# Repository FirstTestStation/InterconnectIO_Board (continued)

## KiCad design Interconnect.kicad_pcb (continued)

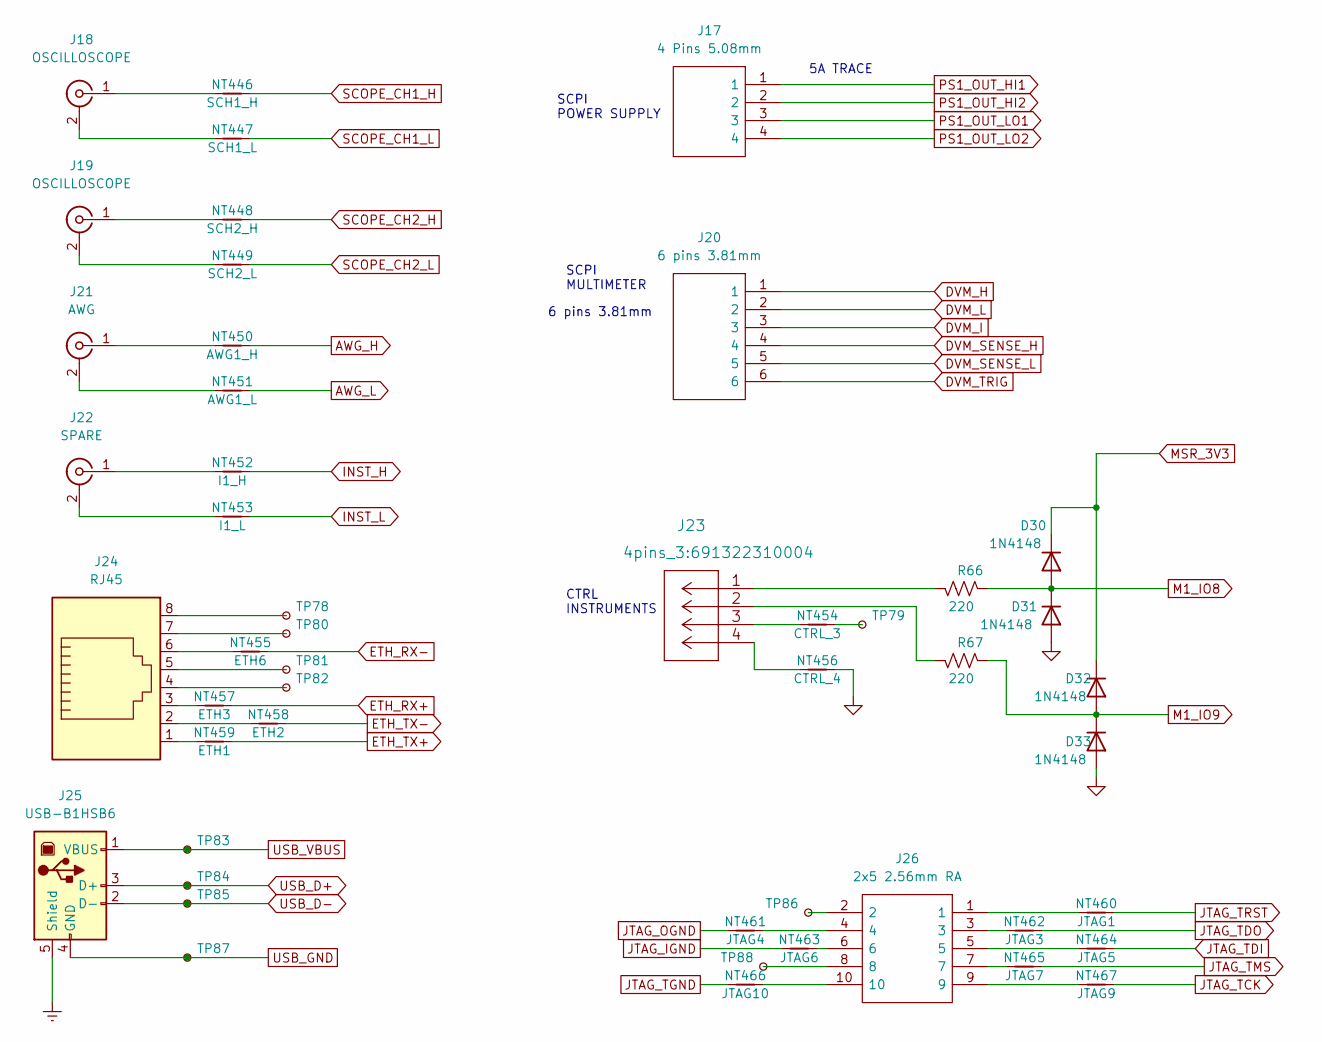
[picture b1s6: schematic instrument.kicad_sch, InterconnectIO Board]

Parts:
D30, D31, D32, D33: 1N4148; D_DO-35_SOD27_P7.62mm_Horizontal
J17: 4 Pins 5.08mm; 1146770000; Manufacturer_Part_Number 1146770000; Mouser Part Number 470-1146770000
J18, J19: OSCILLOSCOPE; BNC_Amphenol_B6252HB-NPP3G-50_Horizontal
J20: 6 pins 3.81mm; SHDRRA6W80P0X381_1X6_2405X920X700P; Manufacturer_Part_Number 691322310006; Mouser Part Number 710-691322310006
J21: AWG; BNC_Amphenol_B6252HB-NPP3G-50_Horizontal
J22: SPARE; BNC_Amphenol_B6252HB-NPP3G-50_Horizontal
J23: 691322310004
J24: RJ45; RJ45_Amphenol_54602-x08_Horizontal
J25: USB-B1HSB6; USB_B_OST_USB-B1HSxx_Horizontal
J26: 2x5 2.56mm RA; SHDRRA10W64P254_2X5_1270X910X880P; Manufacturer_Part_Number SBH11-PBPC-D05-RA-BK
NT446: SCH1_H; NetTie-2_Front1.0mm
NT447: SCH1_L; NetTie-2_Front1.0mm
NT448: SCH2_H; NetTie-2_Front1.0mm
NT449: SCH2_L; NetTie-2_Front1.0mm
NT450: AWG1_H; NetTie-2_Front1.0mm
NT451: AWG1_L; NetTie-2_Front1.0mm
NT452: I1_H; NetTie-2_Front1.0mm
NT453: I1_L; NetTie-2_Front1.0mm
NT454: CTRL_3; NetTie-2_Front1.0mm
NT455: ETH6; NetTie-2_Front1.0mm
NT456: CTRL_4; NetTie-2_Front1.0mm
NT457: ETH3; NetTie-2_Front1.0mm
NT458: ETH2; NetTie-2_Front1.0mm
NT459: ETH1; NetTie-2_Front1.0mm
NT460: JTAG1; NetTie-2_Front1.0mm
NT461: JTAG4; NetTie-2_Front1.0mm
NT462: JTAG3; NetTie-2_Front1.0mm
NT463: JTAG6; NetTie-2_Front1.0mm
NT464: JTAG5; NetTie-2_Front1.0mm
NT465: JTAG7; NetTie-2_Front1.0mm
NT466: JTAG10; NetTie-2_Front1.0mm
NT467: JTAG9; NetTie-2_Front1.0mm
R66, R67: 220; R_Axial_DIN0309_L9.0mm_D3.2mm_P12.70mm_Horizontal
TP78, TP79, TP80, TP81, TP82, TP83, TP84, TP85, TP86, TP87, TP88: TestPoint_Small; Pin_D0.9mm_L10.0mm_W2.4mm_FlatFork

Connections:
AWG_H: NT450.1; also elsewhere on the board
AWG_L: NT451.1; also elsewhere on the board
DVM_H: J20.1; also elsewhere on the board
DVM_I: J20.3; also elsewhere on the board
DVM_L: J20.2; also elsewhere on the board
DVM_SENSE_H: J20.4; also elsewhere on the board
DVM_SENSE_L: J20.5; also elsewhere on the board
DVM_TRIG: J20.6; also elsewhere on the board
ETH_RX+: NT457.1; also elsewhere on the board
ETH_RX-: NT455.1; also elsewhere on the board
ETH_TX+: NT459.1; also elsewhere on the board
ETH_TX-: NT458.1; also elsewhere on the board
Earth: J25.5 (Shield); also elsewhere on the board
GND: D31.2 (A), D33.2 (A), NT456.1; also elsewhere on the board
INST_H: NT452.1; also elsewhere on the board
INST_L: NT453.1; also elsewhere on the board
JTAG_IGND: NT463.1; also elsewhere on the board
JTAG_OGND: NT461.1; also elsewhere on the board
JTAG_TCK: NT467.1; also elsewhere on the board
JTAG_TDI: NT464.1; also elsewhere on the board
JTAG_TDO: NT462.1; also elsewhere on the board
JTAG_TGND: NT466.1; also elsewhere on the board
JTAG_TMS: NT465.1; also elsewhere on the board
JTAG_TRST: NT460.1; also elsewhere on the board
M1_IO8: D30.2 (A), D31.1 (K), R66.1; also elsewhere on the board
M1_IO9: D32.2 (A), D33.1 (K), R67.1; also elsewhere on the board
MSR_3V3: D30.1 (K), D32.1 (K); also elsewhere on the board
unnamed: J18.1 (In), NT446.2
unnamed: J18.2 (Ext), NT447.2
unnamed: J19.1 (In), NT448.2
unnamed: J19.2 (Ext), NT449.2
unnamed: J21.1 (In), NT450.2
unnamed: J21.2 (Ext), NT451.2
unnamed: J22.1 (In), NT452.2
unnamed: J22.2 (Ext), NT453.2
unnamed: J23.1, R66.2
unnamed: J23.2, R67.2
unnamed: J23.3, NT454.2
unnamed: J23.4, NT456.2
unnamed: J24.1, NT459.2
unnamed: J24.2, NT458.2
unnamed: J24.3, NT457.2
unnamed: J24.4, TP82.1
unnamed: J24.5, TP81.1
unnamed: J24.6, NT455.2
unnamed: J24.7, TP80.1
unnamed: J24.8, TP78.1
unnamed: J26.1, NT460.2
unnamed: J26.2, TP86.1
unnamed: J26.3, NT462.2
unnamed: J26.4, NT461.2
unnamed: J26.5, NT464.2
unnamed: J26.6, NT463.2
unnamed: J26.7, NT465.2
unnamed: J26.8, TP88.1
unnamed: J26.9, NT467.2
unnamed: J26.10, NT466.2
unnamed: NT454.1, TP79.1
PS1_OUT_HI1: J17.1; also elsewhere on the board
PS1_OUT_HI2: J17.2; also elsewhere on the board
PS1_OUT_LO1: J17.3; also elsewhere on the board
PS1_OUT_LO2: J17.4; also elsewhere on the board
SCOPE_CH1_H: NT446.1; also elsewhere on the board
SCOPE_CH1_L: NT447.1; also elsewhere on the board
SCOPE_CH2_H: NT448.1; also elsewhere on the board
SCOPE_CH2_L: NT449.1; also elsewhere on the board
USB_D+: J25.3 (D+), TP84.1; also elsewhere on the board
USB_D-: J25.2 (D-), TP85.1; also elsewhere on the board
USB_GND: J25.4 (GND), TP87.1; also elsewhere on the board
USB_VBUS: J25.1 (VBUS), TP83.1; also elsewhere on the board

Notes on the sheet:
SCPI POWER SUPPLY
5A TRACE
CTRL INSTRUMENTS
SCPI MULTIMETER
6 pins 3.81mm

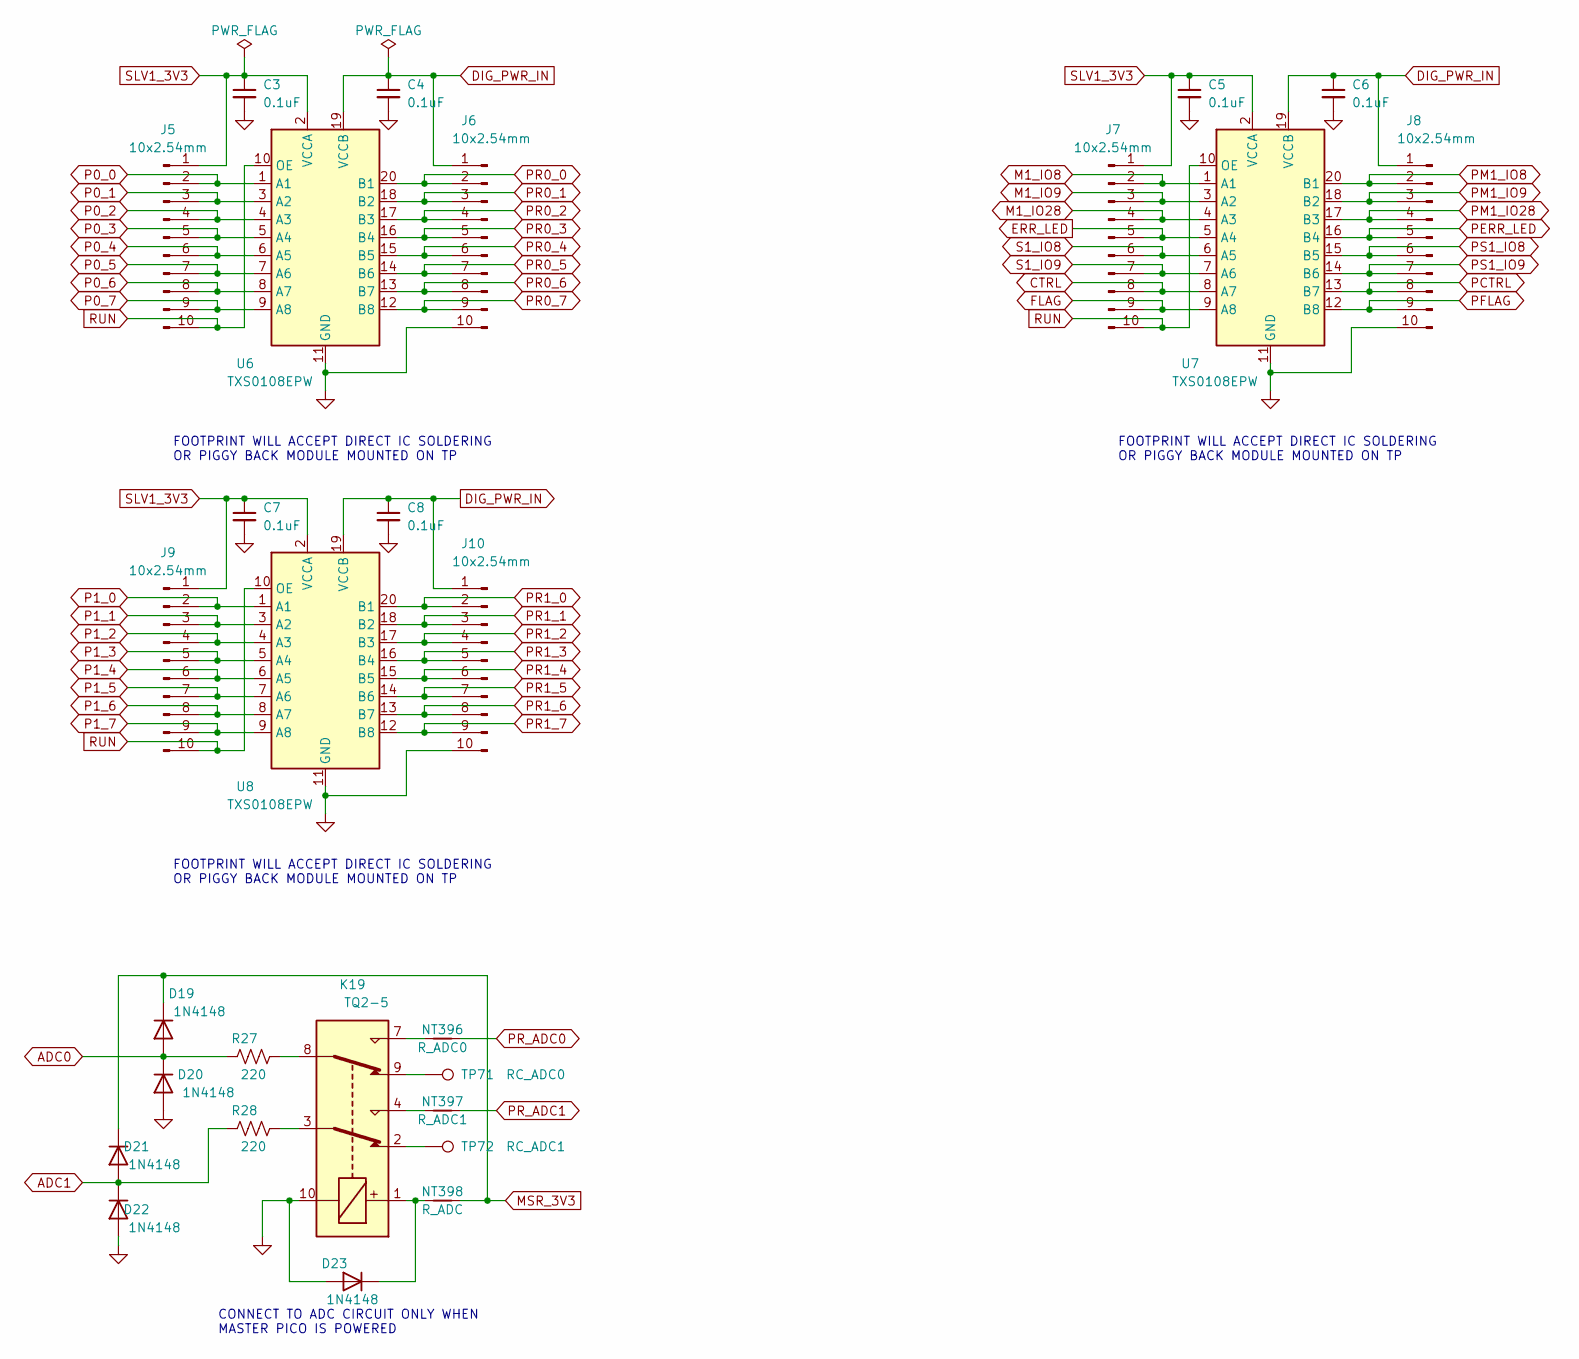
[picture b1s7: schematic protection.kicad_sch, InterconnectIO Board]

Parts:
C3, C4, C5, C6, C7, C8: 0.1uF; C_0603_1608Metric_Pad1.08x0.95mm_HandSolder
D19, D20, D21, D22, D23: 1N4148; D_DO-35_SOD27_P7.62mm_Horizontal
J5, J6, J7, J8, J9, J10: 10x2.54mm; PinHeader_1x10_P2.54mm_Vertical
K19: TQ2-5; Relay_DPDT_FRT5
NT396: R_ADC0; NetTie-2_Front1.0mm
NT397: R_ADC1; NetTie-2_Front1.0mm
NT398: R_ADC; NetTie-2_Front1.0mm
R27, R28: 220; R_Axial_DIN0309_L9.0mm_D3.2mm_P12.70mm_Horizontal
TP71: RC_ADC0; Pin_D0.9mm_L10.0mm_W2.4mm_FlatFork
TP72: RC_ADC1; Pin_D0.9mm_L10.0mm_W2.4mm_FlatFork
U6, U7, U8: TXS0108EPW; TSSOP-20_4.4x6.5mm_P0.65mm

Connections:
ADC0: D19.2 (A), D20.1 (K), R27.1; also elsewhere on the board
ADC1: D21.2 (A), D22.1 (K), R28.1; also elsewhere on the board
CTRL: J7.8, U7.8 (A7); also elsewhere on the board
DIG_PWR_IN: C4.1, C6.1, C8.1, J6.1, J8.1, J10.1, U6.19 (VCCB), U7.19 (VCCB), U8.19 (VCCB); also elsewhere on the board
ERR_LED: J7.5, U7.5 (A4); also elsewhere on the board
FLAG: J7.9, U7.9 (A8); also elsewhere on the board
GND: C3.2, C4.2, C5.2, C6.2, C7.2, C8.2, D20.2 (A), D22.2 (A), D23.2 (A), J6.10, J8.10, J10.10, K19.10, U6.11 (GND), U7.11 (GND), U8.11 (GND); also elsewhere on the board
M1_IO8: J7.2, U7.1 (A1); also elsewhere on the board
M1_IO9: J7.3, U7.3 (A2); also elsewhere on the board
M1_IO28: J7.4, U7.4 (A3); also elsewhere on the board
MSR_3V3: D19.1 (K), D21.1 (K), NT398.1; also elsewhere on the board
unnamed: D23.1 (K), K19.1, NT398.2
unnamed: K19.2, TP72.1
unnamed: K19.3, R28.2
unnamed: K19.4, NT397.2
unnamed: K19.7, NT396.2
unnamed: K19.8, R27.2
unnamed: K19.9, TP71.1
P0_0: J5.2, U6.1 (A1); also elsewhere on the board
P0_1: J5.3, U6.3 (A2); also elsewhere on the board
P0_2: J5.4, U6.4 (A3); also elsewhere on the board
P0_3: J5.5, U6.5 (A4); also elsewhere on the board
P0_4: J5.6, U6.6 (A5); also elsewhere on the board
P0_5: J5.7, U6.7 (A6); also elsewhere on the board
P0_6: J5.8, U6.8 (A7); also elsewhere on the board
P0_7: J5.9, U6.9 (A8); also elsewhere on the board
P1_0: J9.2, U8.1 (A1); also elsewhere on the board
P1_1: J9.3, U8.3 (A2); also elsewhere on the board
P1_2: J9.4, U8.4 (A3); also elsewhere on the board
P1_3: J9.5, U8.5 (A4); also elsewhere on the board
P1_4: J9.6, U8.6 (A5); also elsewhere on the board
P1_5: J9.7, U8.7 (A6); also elsewhere on the board
P1_6: J9.8, U8.8 (A7); also elsewhere on the board
P1_7: J9.9, U8.9 (A8); also elsewhere on the board
PCTRL: J8.8, U7.13 (B7); also elsewhere on the board
PERR_LED: J8.5, U7.16 (B4); also elsewhere on the board
PFLAG: J8.9, U7.12 (B8); also elsewhere on the board
PM1_IO8: J8.2, U7.20 (B1)
PM1_IO9: J8.3, U7.18 (B2)
PM1_IO28: J8.4, U7.17 (B3)
PR0_0: J6.2, U6.20 (B1); also elsewhere on the board
PR0_1: J6.3, U6.18 (B2); also elsewhere on the board
PR0_2: J6.4, U6.17 (B3); also elsewhere on the board
PR0_3: J6.5, U6.16 (B4); also elsewhere on the board
PR0_4: J6.6, U6.15 (B5); also elsewhere on the board
PR0_5: J6.7, U6.14 (B6); also elsewhere on the board
PR0_6: J6.8, U6.13 (B7); also elsewhere on the board
PR0_7: J6.9, U6.12 (B8); also elsewhere on the board
PR1_0: J10.2, U8.20 (B1); also elsewhere on the board
PR1_1: J10.3, U8.18 (B2); also elsewhere on the board
PR1_2: J10.4, U8.17 (B3); also elsewhere on the board
PR1_3: J10.5, U8.16 (B4); also elsewhere on the board
PR1_4: J10.6, U8.15 (B5); also elsewhere on the board
PR1_5: J10.7, U8.14 (B6); also elsewhere on the board
PR1_6: J10.8, U8.13 (B7); also elsewhere on the board
PR1_7: J10.9, U8.12 (B8); also elsewhere on the board
PR_ADC0: NT396.1; also elsewhere on the board
PR_ADC1: NT397.1; also elsewhere on the board
PS1_IO8: J8.6, U7.15 (B5); also elsewhere on the board
PS1_IO9: J8.7, U7.14 (B6); also elsewhere on the board
RUN: J5.10, J7.10, J9.10, U6.10 (OE), U7.10 (OE), U8.10 (OE); also elsewhere on the board
S1_IO8: J7.6, U7.6 (A5); also elsewhere on the board
S1_IO9: J7.7, U7.7 (A6); also elsewhere on the board
SLV1_3V3: C3.1, C5.1, C7.1, J5.1, J7.1, J9.1, U6.2 (VCCA), U7.2 (VCCA), U8.2 (VCCA); also elsewhere on the board

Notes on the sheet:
CONNECT TO ADC CIRCUIT ONLY WHEN MASTER PICO IS POWERED
FOOTPRINT WILL ACCEPT DIRECT IC SOLDERING OR PIGGY BACK MODULE MOUNTED ON TP

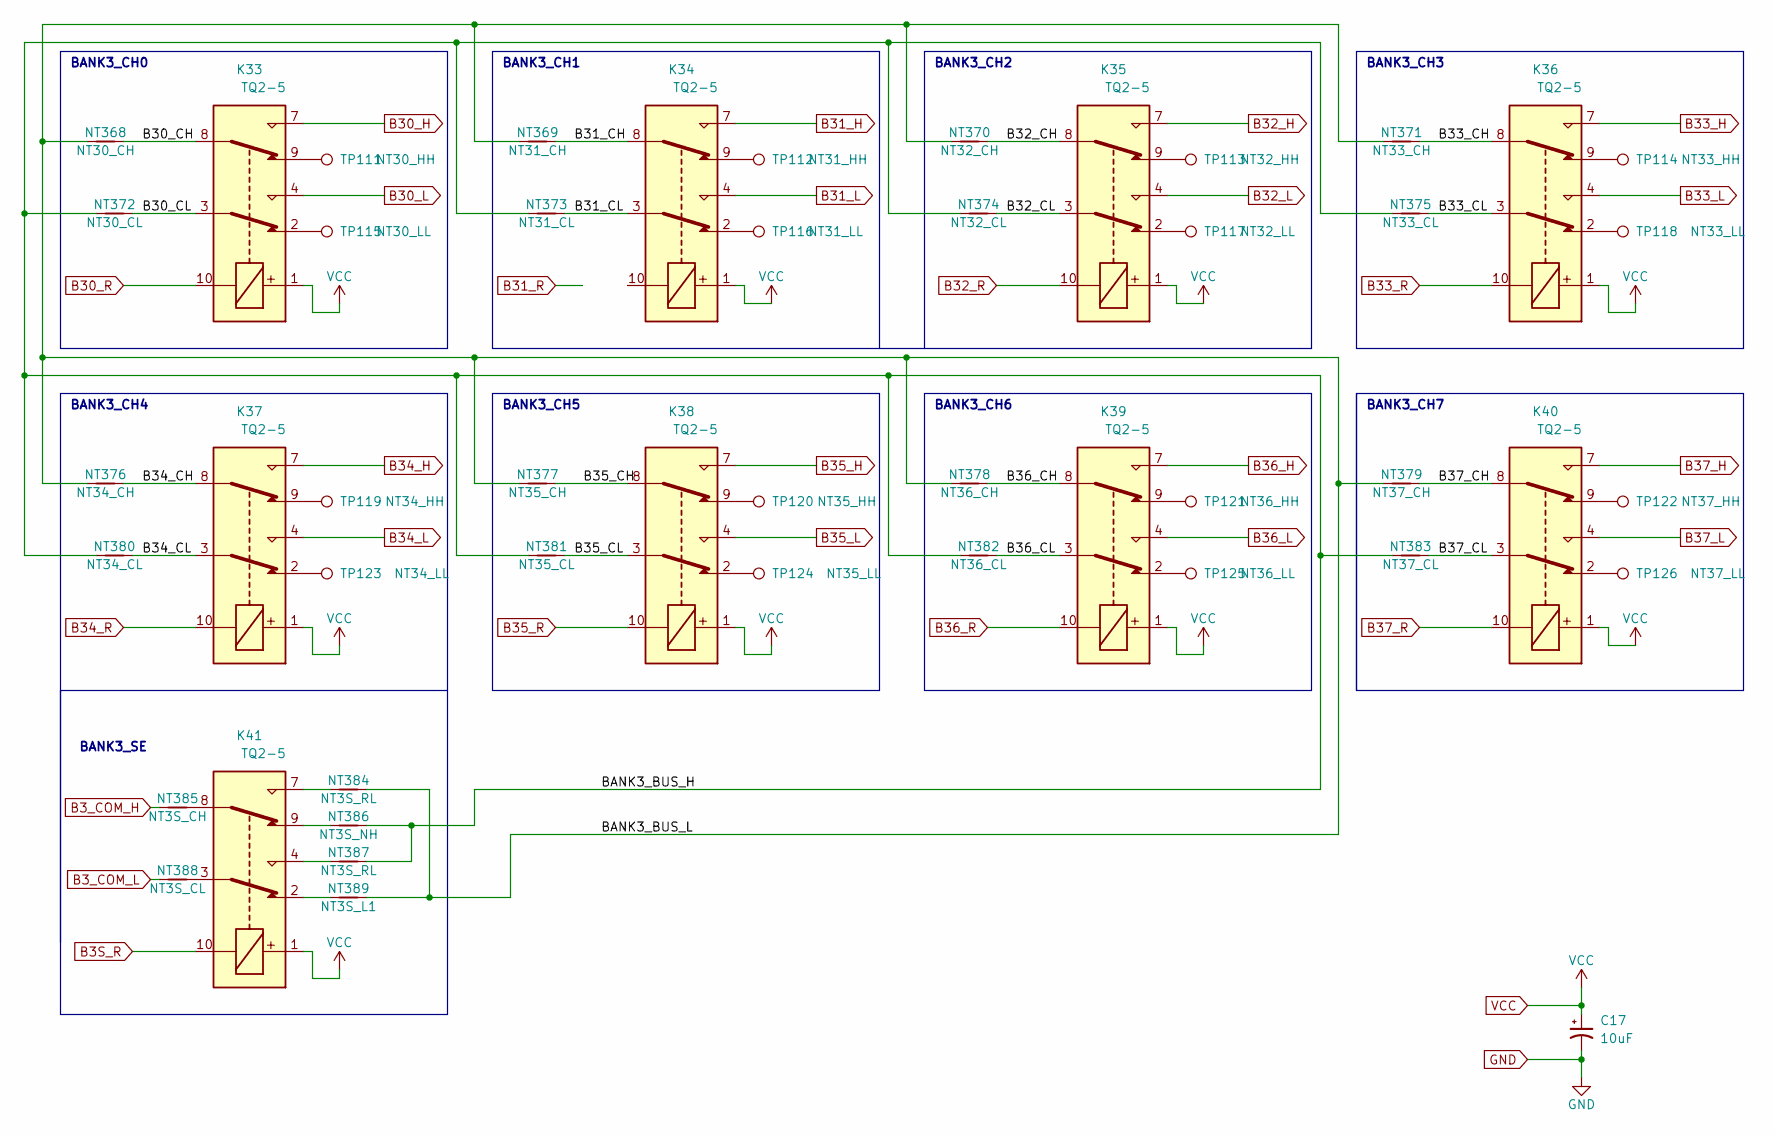
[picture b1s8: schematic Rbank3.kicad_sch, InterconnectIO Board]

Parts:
C17: 10uF; CP_Radial_D4.0mm_P1.50mm
K33, K34, K35, K36, K37, K38, K39, K40, K41: TQ2-5; Relay_DPDT_FRT5
NT368: NT30_CH; NetTie-2_Front1.0mm
NT369: NT31_CH; NetTie-2_Front1.0mm
NT370: NT32_CH; NetTie-2_Front1.0mm
NT371: NT33_CH; NetTie-2_Front1.0mm
NT372: NT30_CL; NetTie-2_Front1.0mm
NT373: NT31_CL; NetTie-2_Front1.0mm
NT374: NT32_CL; NetTie-2_Front1.0mm
NT375: NT33_CL; NetTie-2_Front1.0mm
NT376: NT34_CH; NetTie-2_Front1.0mm
NT377: NT35_CH; NetTie-2_Front1.0mm
NT378: NT36_CH; NetTie-2_Front1.0mm
NT379: NT37_CH; NetTie-2_Front1.0mm
NT380: NT34_CL; NetTie-2_Front1.0mm
NT381: NT35_CL; NetTie-2_Front1.0mm
NT382: NT36_CL; NetTie-2_Front1.0mm
NT383: NT37_CL; NetTie-2_Front1.0mm
NT384, NT387: NT3S_RL; NetTie-2_Front1.0mm
NT385: NT3S_CH; NetTie-2_Front1.0mm
NT386: NT3S_NH; NetTie-2_Front1.0mm
NT388: NT3S_CL; NetTie-2_Front1.0mm
NT389: NT3S_L1; NetTie-2_Front1.0mm
TP111: NT30_HH; Pin_D0.9mm_L10.0mm_W2.4mm_FlatFork
TP112: NT31_HH; Pin_D0.9mm_L10.0mm_W2.4mm_FlatFork
TP113: NT32_HH; Pin_D0.9mm_L10.0mm_W2.4mm_FlatFork
TP114: NT33_HH; Pin_D0.9mm_L10.0mm_W2.4mm_FlatFork
TP115: NT30_LL; Pin_D0.9mm_L10.0mm_W2.4mm_FlatFork
TP116: NT31_LL; Pin_D0.9mm_L10.0mm_W2.4mm_FlatFork
TP117: NT32_LL; Pin_D0.9mm_L10.0mm_W2.4mm_FlatFork
TP118: NT33_LL; Pin_D0.9mm_L10.0mm_W2.4mm_FlatFork
TP119: NT34_HH; Pin_D0.9mm_L10.0mm_W2.4mm_FlatFork
TP120: NT35_HH; Pin_D0.9mm_L10.0mm_W2.4mm_FlatFork
TP121: NT36_HH; Pin_D0.9mm_L10.0mm_W2.4mm_FlatFork
TP122: NT37_HH; Pin_D0.9mm_L10.0mm_W2.4mm_FlatFork
TP123: NT34_LL; Pin_D0.9mm_L10.0mm_W2.4mm_FlatFork
TP124: NT35_LL; Pin_D0.9mm_L10.0mm_W2.4mm_FlatFork
TP125: NT36_LL; Pin_D0.9mm_L10.0mm_W2.4mm_FlatFork
TP126: NT37_LL; Pin_D0.9mm_L10.0mm_W2.4mm_FlatFork

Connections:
/Relay_Bank3/B30_CH: K33.8, NT368.2
/Relay_Bank3/B30_CL: K33.3, NT372.2
/Relay_Bank3/B31_CH: K34.8, NT369.2
/Relay_Bank3/B31_CL: K34.3, NT373.2
/Relay_Bank3/B32_CH: K35.8, NT370.2
/Relay_Bank3/B32_CL: K35.3, NT374.2
/Relay_Bank3/B33_CH: K36.8, NT371.2
/Relay_Bank3/B33_CL: K36.3, NT375.2
/Relay_Bank3/B34_CH: K37.8, NT376.2
/Relay_Bank3/B34_CL: K37.3, NT380.2
/Relay_Bank3/B35_CH: K38.8, NT377.2
/Relay_Bank3/B35_CL: K38.3, NT381.2
/Relay_Bank3/B36_CH: K39.8, NT378.2
/Relay_Bank3/B36_CL: K39.3, NT382.2
/Relay_Bank3/B37_CH: K40.8, NT379.2
/Relay_Bank3/B37_CL: K40.3, NT383.2
/Relay_Bank3/BANK3_BUS_H: NT372.1, NT373.1, NT374.1, NT375.1, NT380.1, NT381.1, NT382.1, NT383.1, NT386.2, NT387.2
/Relay_Bank3/BANK3_BUS_L: NT368.1, NT369.1, NT370.1, NT371.1, NT376.1, NT377.1, NT378.1, NT379.1, NT384.2, NT389.2
B3S_R: K41.10; also elsewhere on the board
B3_COM_H: NT385.1; also elsewhere on the board
B3_COM_L: NT388.1; also elsewhere on the board
B30_H: K33.7; also elsewhere on the board
B30_L: K33.4; also elsewhere on the board
B30_R: K33.10; also elsewhere on the board
B31_H: K34.7; also elsewhere on the board
B31_L: K34.4; also elsewhere on the board
B32_H: K35.7; also elsewhere on the board
B32_L: K35.4; also elsewhere on the board
B32_R: K35.10; also elsewhere on the board
B33_H: K36.7; also elsewhere on the board
B33_L: K36.4; also elsewhere on the board
B33_R: K36.10; also elsewhere on the board
B34_H: K37.7; also elsewhere on the board
B34_L: K37.4; also elsewhere on the board
B34_R: K37.10; also elsewhere on the board
B35_H: K38.7; also elsewhere on the board
B35_L: K38.4; also elsewhere on the board
B35_R: K38.10; also elsewhere on the board
B36_H: K39.7; also elsewhere on the board
B36_L: K39.4; also elsewhere on the board
B36_R: K39.10; also elsewhere on the board
B37_H: K40.7; also elsewhere on the board
B37_L: K40.4; also elsewhere on the board
B37_R: K40.10; also elsewhere on the board
GND: C17.2; also elsewhere on the board
unnamed: K33.2, TP115.1
unnamed: K33.9, TP111.1
unnamed: K34.2, TP116.1
unnamed: K34.9, TP112.1
unnamed: K35.2, TP117.1
unnamed: K35.9, TP113.1
unnamed: K36.2, TP118.1
unnamed: K36.9, TP114.1
unnamed: K37.2, TP123.1
unnamed: K37.9, TP119.1
unnamed: K38.2, TP124.1
unnamed: K38.9, TP120.1
unnamed: K39.2, TP125.1
unnamed: K39.9, TP121.1
unnamed: K40.2, TP126.1
unnamed: K40.9, TP122.1
unnamed: K41.2, NT389.1
unnamed: K41.3, NT388.2
unnamed: K41.4, NT387.1
unnamed: K41.7, NT384.1
unnamed: K41.8, NT385.2
unnamed: K41.9, NT386.1
PWR_5V: C17.1, K33.1, K34.1, K35.1, K36.1, K37.1, K38.1, K39.1, K40.1, K41.1; also elsewhere on the board

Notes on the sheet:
BANK3_SE
BANK3_CH6
BANK3_CH5
BANK3_CH1
BANK3_CH4
BANK3_CH3
BANK3_CH7
BANK3_CH0
BANK3_CH2

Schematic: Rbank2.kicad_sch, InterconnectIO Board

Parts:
C16: 10uF; CP_Radial_D4.0mm_P1.50mm
K24, K25, K26, K27, K28, K29, K30, K31, K32: TQ2-5; Relay_DPDT_FRT5
NT45: NT20_CH; NetTie-2_Front1.0mm
NT46: NT21_CH; NetTie-2_Front1.0mm
NT47: NT22_CH; NetTie-2_Front1.0mm
NT349: NT23_CH; NetTie-2_Front1.0mm
NT350: NT20_CL; NetTie-2_Front1.0mm
NT351: NT21_CL; NetTie-2_Front1.0mm
NT352: NT22_CL; NetTie-2_Front1.0mm
NT353: NT23_CL; NetTie-2_Front1.0mm
NT354: NT24_CH; NetTie-2_Front1.0mm
NT355: NT25_CH; NetTie-2_Front1.0mm
NT356: NT26_CH; NetTie-2_Front1.0mm
NT357: NT27_CH; NetTie-2_Front1.0mm
NT358: NT24_CL; NetTie-2_Front1.0mm
NT359: NT25_CL; NetTie-2_Front1.0mm
NT360: NT26_CL; NetTie-2_Front1.0mm
NT361: NT27_CL; NetTie-2_Front1.0mm
NT362, NT365: NT2S_RL; NetTie-2_Front1.0mm
NT363: NT2S_CH; NetTie-2_Front1.0mm
NT364: NT2S_NH; NetTie-2_Front1.0mm
NT366: NT2S_CL; NetTie-2_Front1.0mm
NT367: NT2S_L1; NetTie-2_Front1.0mm
TP89: NT20_HH; Pin_D0.9mm_L10.0mm_W2.4mm_FlatFork
TP90: NT21_HH; Pin_D0.9mm_L10.0mm_W2.4mm_FlatFork
TP91: NT22_HH; Pin_D0.9mm_L10.0mm_W2.4mm_FlatFork
TP93: NT23_HH; Pin_D0.9mm_L10.0mm_W2.4mm_FlatFork
TP95: NT20_LL; Pin_D0.9mm_L10.0mm_W2.4mm_FlatFork
TP96: NT21_LL; Pin_D0.9mm_L10.0mm_W2.4mm_FlatFork
TP99: NT22_LL; Pin_D0.9mm_L10.0mm_W2.4mm_FlatFork
TP102: NT23_LL; Pin_D0.9mm_L10.0mm_W2.4mm_FlatFork
TP103: NT24_HH; Pin_D0.9mm_L10.0mm_W2.4mm_FlatFork
TP104: NT25_HH; Pin_D0.9mm_L10.0mm_W2.4mm_FlatFork
TP105: NT26_HH; Pin_D0.9mm_L10.0mm_W2.4mm_FlatFork
TP106: NT27_HH; Pin_D0.9mm_L10.0mm_W2.4mm_FlatFork
TP107: NT24_LL; Pin_D0.9mm_L10.0mm_W2.4mm_FlatFork
TP108: NT25_LL; Pin_D0.9mm_L10.0mm_W2.4mm_FlatFork
TP109: NT26_LL; Pin_D0.9mm_L10.0mm_W2.4mm_FlatFork
TP110: NT27_LL; Pin_D0.9mm_L10.0mm_W2.4mm_FlatFork

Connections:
/Relay_Bank2/B20_CH: K24.8, NT45.2
/Relay_Bank2/B20_CL: K24.3, NT350.2
/Relay_Bank2/B21_CH: K25.8, NT46.2
/Relay_Bank2/B21_CL: K25.3, NT351.2
/Relay_Bank2/B22_CH: K26.8, NT47.2
/Relay_Bank2/B22_CL: K26.3, NT352.2
/Relay_Bank2/B23_CH: K27.8, NT349.2
/Relay_Bank2/B23_CL: K27.3, NT353.2
/Relay_Bank2/B24_CH: K28.8, NT354.2
/Relay_Bank2/B24_CL: K28.3, NT358.2
/Relay_Bank2/B25_CH: K29.8, NT355.2
/Relay_Bank2/B25_CL: K29.3, NT359.2
/Relay_Bank2/B26_CH: K30.8, NT356.2
/Relay_Bank2/B26_CL: K30.3, NT360.2
/Relay_Bank2/B27_CH: K31.8, NT357.2
/Relay_Bank2/B27_CL: K31.3, NT361.2
/Relay_Bank2/BANK2_BUS_H: NT350.1, NT351.1, NT352.1, NT353.1, NT358.1, NT359.1, NT360.1, NT361.1, NT364.2, NT365.2
/Relay_Bank2/BANK2_BUS_L: NT45.1, NT46.1, NT47.1, NT349.1, NT354.1, NT355.1, NT356.1, NT357.1, NT362.2, NT367.2
B2S_R: K32.10; also elsewhere on the board
B2_COM_H: NT363.1; also elsewhere on the board
B2_COM_L: NT366.1; also elsewhere on the board
B20_H: K24.7; also elsewhere on the board
B20_L: K24.4; also elsewhere on the board
B20_R: K24.10; also elsewhere on the board
B21_H: K25.7; also elsewhere on the board
B21_L: K25.4; also elsewhere on the board
B21_R: K25.10; also elsewhere on the board
B22_H: K26.7; also elsewhere on the board
B22_L: K26.4; also elsewhere on the board
B22_R: K26.10; also elsewhere on the board
B23_H: K27.7; also elsewhere on the board
B23_L: K27.4; also elsewhere on the board
B23_R: K27.10; also elsewhere on the board
B24_H: K28.7; also elsewhere on the board
B24_L: K28.4; also elsewhere on the board
B24_R: K28.10; also elsewhere on the board
B25_H: K29.7; also elsewhere on the board
B25_L: K29.4; also elsewhere on the board
B25_R: K29.10; also elsewhere on the board
B26_H: K30.7; also elsewhere on the board
B26_L: K30.4; also elsewhere on the board
B26_R: K30.10; also elsewhere on the board
B27_H: K31.7; also elsewhere on the board
B27_L: K31.4; also elsewhere on the board
B27_R: K31.10; also elsewhere on the board
GND: C16.2; also elsewhere on the board
unnamed: K24.2, TP95.1
unnamed: K24.9, TP89.1
unnamed: K25.2, TP96.1
unnamed: K25.9, TP90.1
unnamed: K26.2, TP99.1
unnamed: K26.9, TP91.1
unnamed: K27.2, TP102.1
unnamed: K27.9, TP93.1
unnamed: K28.2, TP107.1
unnamed: K28.9, TP103.1
unnamed: K29.2, TP108.1
unnamed: K29.9, TP104.1
unnamed: K30.2, TP109.1
unnamed: K30.9, TP105.1
unnamed: K31.2, TP110.1
unnamed: K31.9, TP106.1
unnamed: K32.2, NT367.1
unnamed: K32.3, NT366.2
unnamed: K32.4, NT365.1
unnamed: K32.7, NT362.1
unnamed: K32.8, NT363.2
unnamed: K32.9, NT364.1
PWR_5V: C16.1, K24.1, K25.1, K26.1, K27.1, K28.1, K29.1, K30.1, K31.1, K32.1; also elsewhere on the board

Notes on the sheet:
BANK2_CH1
BANK2_SE
BANK2_CH4
BANK2_CH6
BANK2_CH7
BANK2_CH3
BANK2_CH5
BANK2_CH0
BANK2_CH2
